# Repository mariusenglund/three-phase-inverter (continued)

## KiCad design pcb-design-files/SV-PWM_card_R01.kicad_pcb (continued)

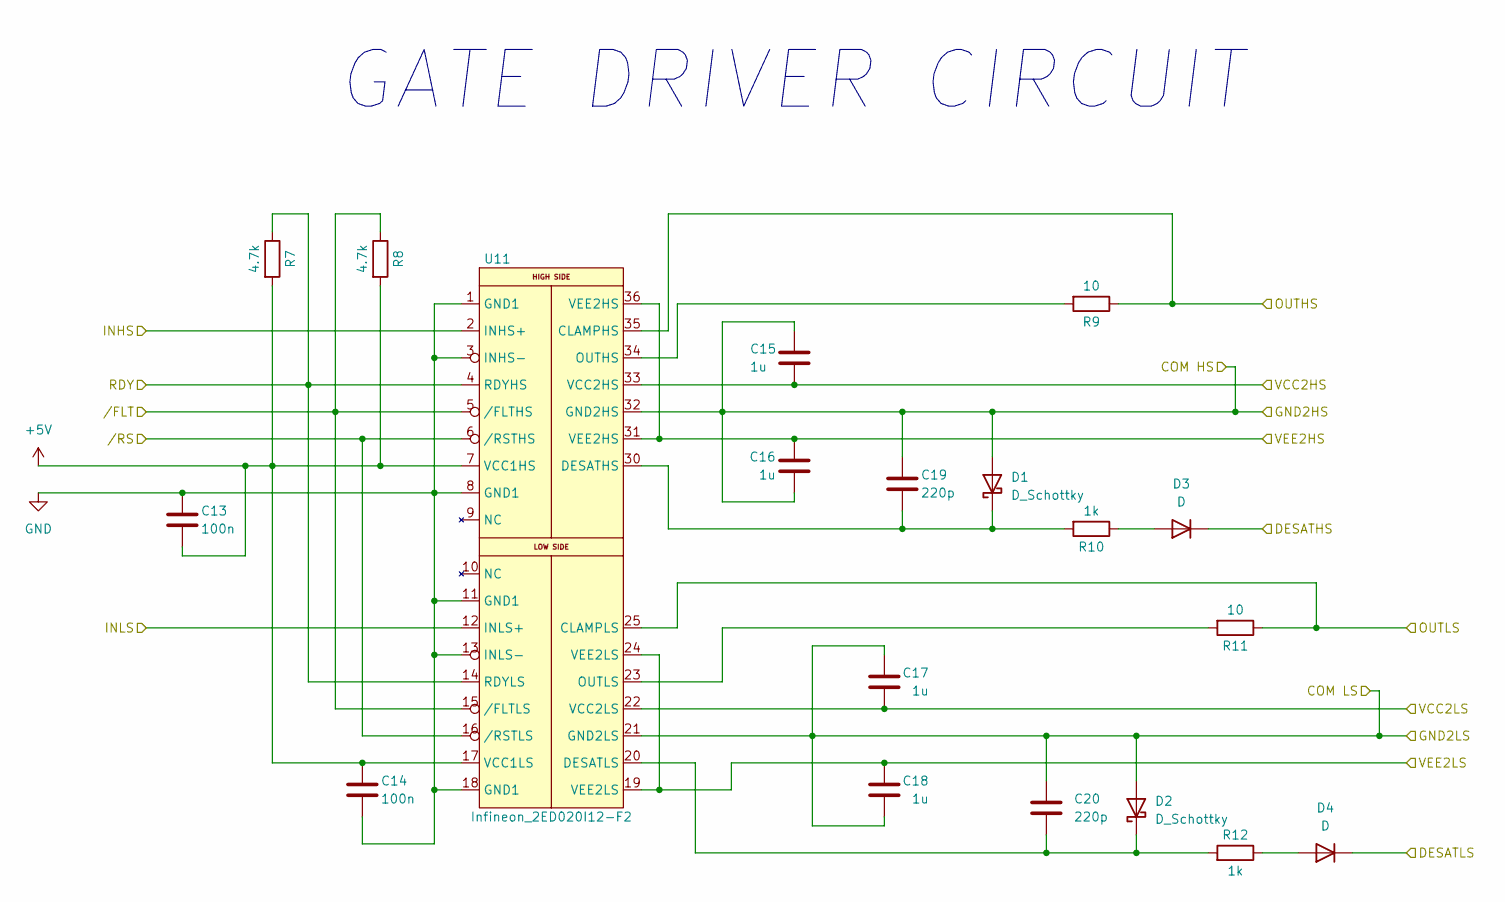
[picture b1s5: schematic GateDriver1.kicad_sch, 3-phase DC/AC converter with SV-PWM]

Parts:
C13, C14: 100n; C_1206_3216Metric_Pad1.33x1.80mm_HandSolder
C15, C16, C17, C18: 1u; C_1206_3216Metric_Pad1.33x1.80mm_HandSolder
C19, C20: 220p; C_1206_3216Metric_Pad1.33x1.80mm_HandSolder
D1, D2: D_Schottky; Schottky-BAT165AX
D3, D4: D; Diode-SMBJ50CA
R7, R8: 4.7k; R_1206_3216Metric_Pad1.30x1.75mm_HandSolder
R9, R11: 10; R_1206_3216Metric_Pad1.30x1.75mm_HandSolder
R10, R12: 1k; R_1206_3216Metric_Pad1.30x1.75mm_HandSolder
U11: Infineon_2ED020I12-F2; GateDriver-2ED020I12F2XUMA1

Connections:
+5V: C13.1, C14.2, R7.2, R8.2, U11.7 (VCC1HS), U11.17 (VCC1LS); also elsewhere on the board
+15 V (1): C17.1, U11.22 (VCC2LS); also elsewhere on the board
+15 V (2): C15.2, U11.33 (VCC2HS); also elsewhere on the board
-8.7 V (1): C18.1, U11.19 (VEE2LS), U11.24 (VEE2LS); also elsewhere on the board
-8.7 V (2): C16.1, U11.31 (VEE2HS), U11.36 (VEE2HS); also elsewhere on the board
/GateDriver1/OUTHS: R9.1, U11.35 (CLAMPHS); also elsewhere on the board
/GateDriver1/OUTLS: R11.1, U11.25 (CLAMPLS); also elsewhere on the board
COM (2): C15.1, C16.2, C19.2, D1.2 (A), D4.1 (K), U11.32 (GND2HS); also elsewhere on the board
GND: C13.2, C14.1, U11.1 (GND1), U11.3 (INHS-), U11.8 (GND1), U11.11 (GND1), U11.13 (INLS-), U11.18 (GND1); also elsewhere on the board
GND (dc-link): C17.2, C18.2, C20.2, D2.2 (A), U11.21 (GND2LS); also elsewhere on the board
I/O_DI_FLT-1: R8.1, U11.5 (/FLTHS), U11.15 (/FLTLS); also elsewhere on the board
I/O_DI_RDY-1: R7.1, U11.4 (RDYHS), U11.14 (RDYLS); also elsewhere on the board
I/O_DO_INHS-1: U11.2 (INHS+); also elsewhere on the board
I/O_DO_INLS-1: U11.12 (INLS+); also elsewhere on the board
I/O_DO_RS-1: U11.6 (/RSTHS), U11.16 (/RSTLS); also elsewhere on the board
unnamed: C19.1, D1.1 (K), R10.2, U11.30 (DESATHS)
unnamed: C20.1, D2.1 (K), R12.2, U11.20 (DESATLS)
unnamed: D3.2 (A), R10.1
unnamed: D4.2 (A), R12.1
unnamed: R9.2, U11.34 (OUTHS)
unnamed: R11.2, U11.23 (OUTLS)
TA+1_HS: D3.1 (K); also elsewhere on the board

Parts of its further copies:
C21, C22, C29, C30: 100n; C_1206_3216Metric_Pad1.33x1.80mm_HandSolder
C23, C24, C25, C26, C31, C32, C33, C34: 1u; C_1206_3216Metric_Pad1.33x1.80mm_HandSolder
C27, C28, C35, C36: 220p; C_1206_3216Metric_Pad1.33x1.80mm_HandSolder
D5, D6, D9, D10: D_Schottky; Schottky-BAT165AX
D7, D8, D11, D12: D; Diode-SMBJ50CA
R13, R14, R19, R20: 4.7k; R_1206_3216Metric_Pad1.30x1.75mm_HandSolder
R15, R17, R21, R23: 10; R_1206_3216Metric_Pad1.30x1.75mm_HandSolder
R16, R18, R22, R24: 1k; R_1206_3216Metric_Pad1.30x1.75mm_HandSolder
U12, U13: Infineon_2ED020I12-F2; GateDriver-2ED020I12F2XUMA1

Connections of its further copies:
+5V: C21.1, C22.2, C29.1, C30.2, R13.2, R14.2, R19.2, R20.2, U12.7 (VCC1HS), U12.17 (VCC1LS), U13.7 (VCC1HS), U13.17 (VCC1LS); also elsewhere on the board
+15 V (3): C25.1, U12.22 (VCC2LS); also elsewhere on the board
+15 V (4): C23.2, U12.33 (VCC2HS); also elsewhere on the board
+15 V (5): C33.1, U13.22 (VCC2LS); also elsewhere on the board
+15 V (6): C31.2, U13.33 (VCC2HS); also elsewhere on the board
-8.7 V (3): C26.1, U12.19 (VEE2LS), U12.24 (VEE2LS); also elsewhere on the board
-8.7 V (4): C24.1, U12.31 (VEE2HS), U12.36 (VEE2HS); also elsewhere on the board
-8.7 V (5): C34.1, U13.19 (VEE2LS), U13.24 (VEE2LS); also elsewhere on the board
-8.7 V (6): C32.1, U13.31 (VEE2HS), U13.36 (VEE2HS); also elsewhere on the board
/GateDriver2/OUTHS: R15.1, U12.35 (CLAMPHS); also elsewhere on the board
/GateDriver2/OUTLS: R17.1, U12.25 (CLAMPLS); also elsewhere on the board
/GateDriver3/OUTHS: R21.1, U13.35 (CLAMPHS); also elsewhere on the board
/GateDriver3/OUTLS: R23.1, U13.25 (CLAMPLS); also elsewhere on the board
COM (4): C23.1, C24.2, C27.2, D5.2 (A), D8.1 (K), U12.32 (GND2HS); also elsewhere on the board
COM (6): C31.1, C32.2, C35.2, D9.2 (A), D12.1 (K), U13.32 (GND2HS); also elsewhere on the board
GND: C21.2, C22.1, C29.2, C30.1, U12.1 (GND1), U12.3 (INHS-), U12.8 (GND1), U12.11 (GND1), U12.13 (INLS-), U12.18 (GND1), U13.1 (GND1), U13.3 (INHS-), U13.8 (GND1), U13.11 (GND1), U13.13 (INLS-), U13.18 (GND1); also elsewhere on the board
GND (dc-link): C25.2, C26.2, C28.2, C33.2, C34.2, C36.2, D6.2 (A), D10.2 (A), U12.21 (GND2LS), U13.21 (GND2LS); also elsewhere on the board
I/O_DI_FLT-2: R14.1, U12.5 (/FLTHS), U12.15 (/FLTLS); also elsewhere on the board
I/O_DI_FLT-3: R20.1, U13.5 (/FLTHS), U13.15 (/FLTLS); also elsewhere on the board
I/O_DI_RDY-2: R13.1, U12.4 (RDYHS), U12.14 (RDYLS); also elsewhere on the board
I/O_DI_RDY-3: R19.1, U13.4 (RDYHS), U13.14 (RDYLS); also elsewhere on the board
I/O_DO_INHS-2: U12.2 (INHS+); also elsewhere on the board
I/O_DO_INHS-3: U13.2 (INHS+); also elsewhere on the board
I/O_DO_INLS-2: U12.12 (INLS+); also elsewhere on the board
I/O_DO_INLS-3: U13.12 (INLS+); also elsewhere on the board
I/O_DO_RS-2: U12.6 (/RSTHS), U12.16 (/RSTLS); also elsewhere on the board
I/O_DO_RS-3: U13.6 (/RSTHS), U13.16 (/RSTLS); also elsewhere on the board
unnamed: C27.1, D5.1 (K), R16.2, U12.30 (DESATHS)
unnamed: C28.1, D6.1 (K), R18.2, U12.20 (DESATLS)
unnamed: C35.1, D9.1 (K), R22.2, U13.30 (DESATHS)
unnamed: C36.1, D10.1 (K), R24.2, U13.20 (DESATLS)
unnamed: D7.2 (A), R16.1
unnamed: D8.2 (A), R18.1
unnamed: D11.2 (A), R22.1
unnamed: D12.2 (A), R24.1
unnamed: R15.2, U12.34 (OUTHS)
unnamed: R17.2, U12.23 (OUTLS)
unnamed: R21.2, U13.34 (OUTHS)
unnamed: R23.2, U13.23 (OUTLS)
TA+1_HS: D7.1 (K), D11.1 (K); also elsewhere on the board

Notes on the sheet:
GATE DRIVER CIRCUIT

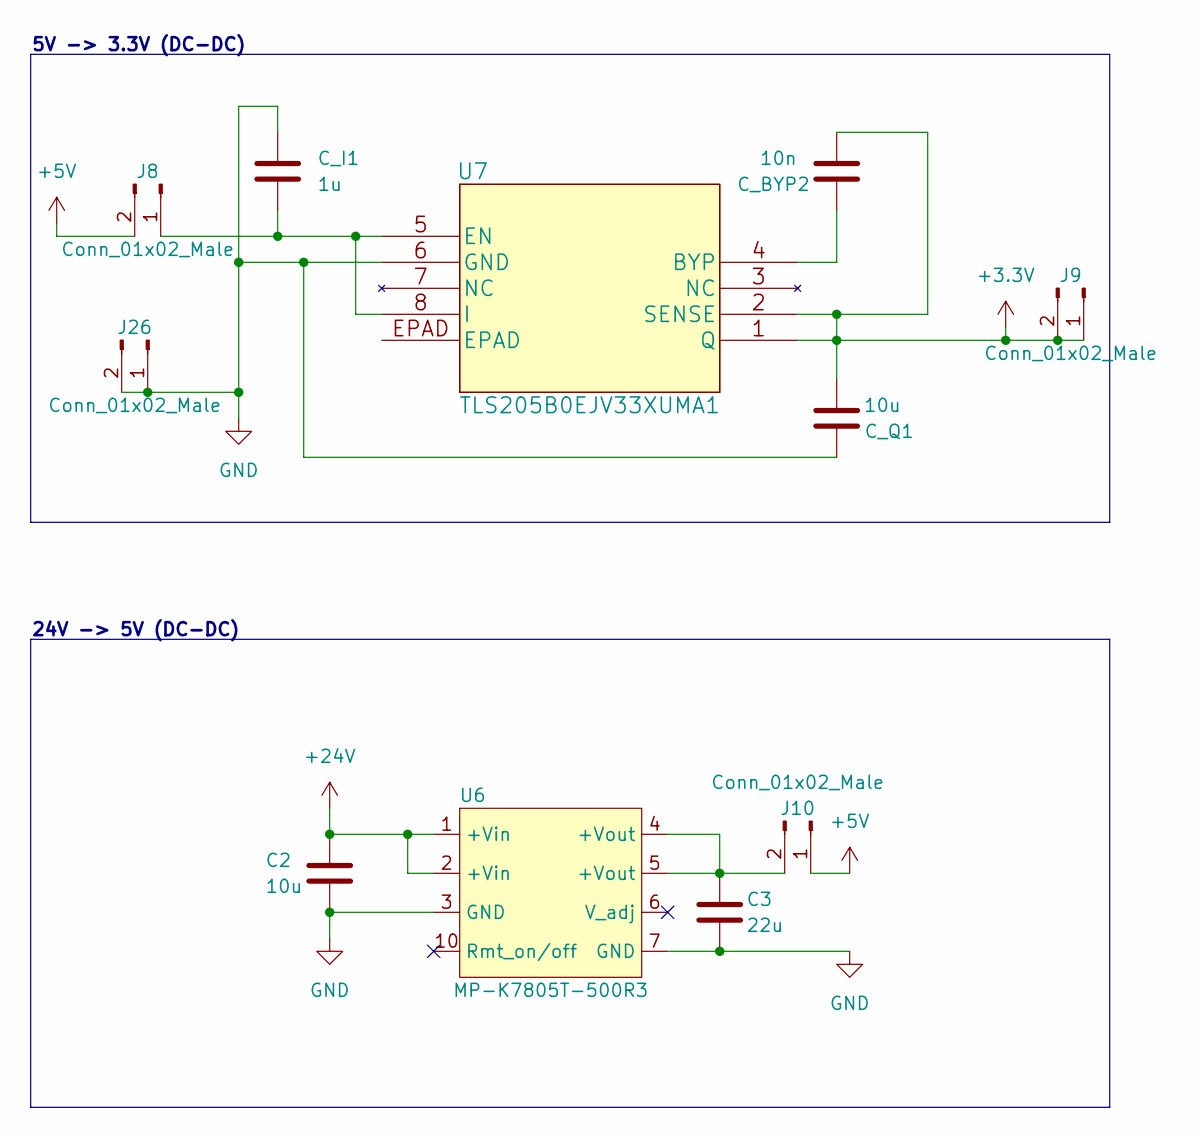
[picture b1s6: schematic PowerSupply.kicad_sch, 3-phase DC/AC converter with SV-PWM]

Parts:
C2: 10u; C_1206_3216Metric_Pad1.33x1.80mm_HandSolder
C3: 22u; C_1206_3216Metric_Pad1.33x1.80mm_HandSolder
C_BYP2: 10n; C_1206_3216Metric_Pad1.33x1.80mm_HandSolder
C_I1: 1u; C_1206_3216Metric_Pad1.33x1.80mm_HandSolder
C_Q1: 10u; C_1206_3216Metric_Pad1.33x1.80mm_HandSolder
J8, J9, J10, J26: Conn_01x02_Male; PinHeader_1x02_P1.00mm_Vertical
U6: MP-K7805T-500R3; Multicomp-MPK7803T500R3
U7: TLS205B0EJV33XUMA1; TLS205B0EJV33XUMA1-SOIC127P600X170-9N

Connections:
+3.3V: C_BYP2.2, C_Q1.2, J9.1, J9.2, U7.1 (Q), U7.2 (SENSE); also elsewhere on the board
+5V: J8.2, J10.1; also elsewhere on the board
+24V: C2.1, U6.1 (+Vin), U6.2 (+Vin); also elsewhere on the board
GND: C2.2, C3.2, C_I1.2, C_Q1.1, J26.1, J26.2, U6.3 (GND), U6.7 (GND), U7.6 (GND); also elsewhere on the board
unnamed: C3.1, J10.2, U6.4 (+Vout), U6.5 (+Vout)
unnamed: C_BYP2.1, U7.4 (BYP)
unnamed: C_I1.1, J8.1, U7.5 (EN), U7.8 (I)

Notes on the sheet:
24V -> 5V (DC-DC)
5V -> 3.3V (DC-DC)

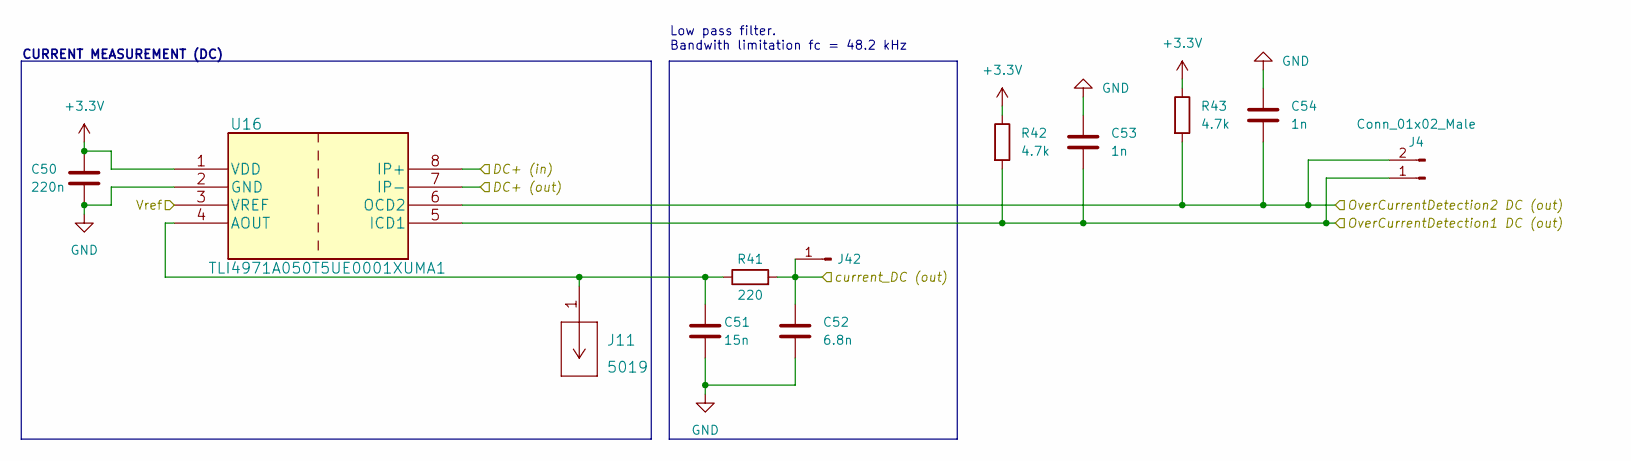
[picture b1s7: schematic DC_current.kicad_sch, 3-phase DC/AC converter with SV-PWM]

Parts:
C50: 220n; C_1206_3216Metric_Pad1.33x1.80mm_HandSolder
C51: 15n; C_1206_3216Metric_Pad1.33x1.80mm_HandSolder
C52: 6.8n; C_1206_3216Metric_Pad1.33x1.80mm_HandSolder
C53, C54: 1n; C_1206_3216Metric_Pad1.33x1.80mm_HandSolder
J4: Conn_01x02_Male; PinHeader_1x02_P1.00mm_Vertical
J11: 5019; Keystone-5019
J42: Conn_01x01_Male; PinHeader_1x01_P1.00mm_Vertical
R41: 220; R_1206_3216Metric_Pad1.30x1.75mm_HandSolder
R42, R43: 4.7k; R_1206_3216Metric_Pad1.30x1.75mm_HandSolder
U16: TLI4971A050T5UE0001XUMA1

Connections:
+3.3V: C50.2, R42.1, R43.1, U16.1 (VDD), U16.9; also elsewhere on the board
/Braking/DC-LINK (+): U16.8 (IP+); also elsewhere on the board
GND: C50.1, C51.2, C52.2, C53.1, C54.1, U16.2 (GND); also elsewhere on the board
I/O_AI_current-dc: C52.1, J42.1, R41.2; also elsewhere on the board
I/O_AI_vcc-io: U16.3 (VREF); also elsewhere on the board
I/O_DI_ocd1-dc: C53.2, J4.1, R42.2, U16.5 (ICD1); also elsewhere on the board
I/O_DI_ocd2-dc: C54.2, J4.2, R43.2, U16.6 (OCD2); also elsewhere on the board
unnamed: C51.1, J11.1, R41.1, U16.4 (AOUT)
TA+1_HS: U16.7 (IP-); also elsewhere on the board

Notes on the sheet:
Low pass filter. Bandwith limitation fc = 48.2 kHz
CURRENT MEASUREMENT (DC)

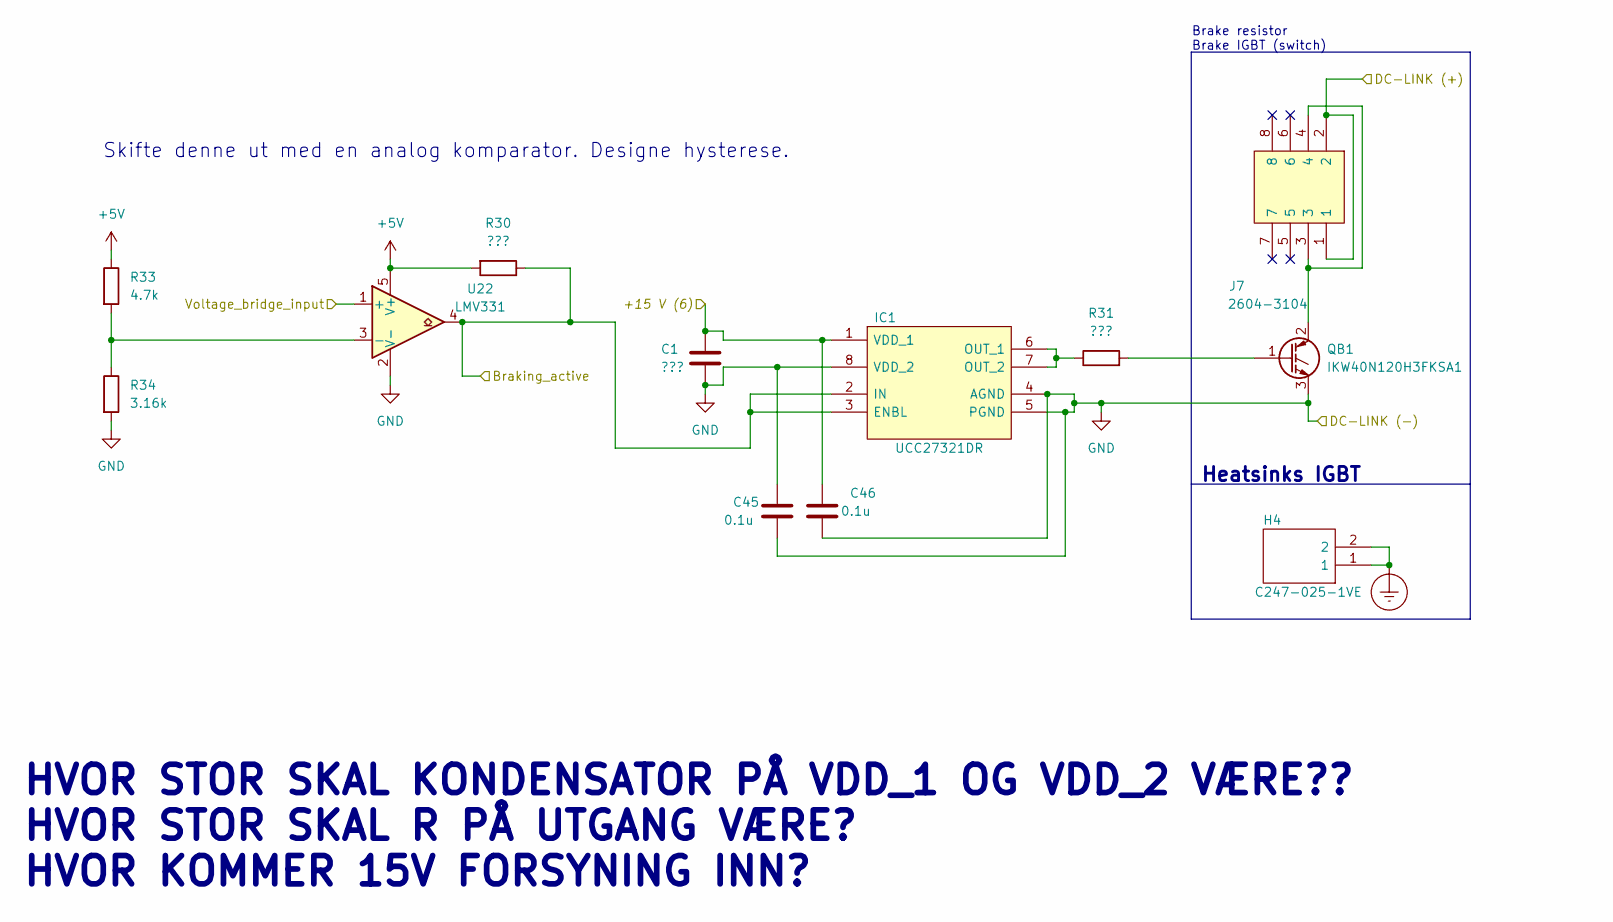
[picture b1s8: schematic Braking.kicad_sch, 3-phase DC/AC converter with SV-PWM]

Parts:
C1: ???; C_1206_3216Metric_Pad1.33x1.80mm_HandSolder
C45, C46: 0.1u; C_1206_3216Metric_Pad1.33x1.80mm_HandSolder
H4: C247-025-1VE; Heatsink_brake_C2470251VE; Manufacturer_Part_Number C247-025-1VE; Mouser Part Number 588-C247-025-1VE
IC1: UCC27321DR; UCC27321DR_SOIC127P600X175-8N; Manufacturer_Part_Number UCC27321DR; Mouser Part Number 595-UCC27321DR
J7: 2604-3104; WAGO-26043104; Manufacturer_Part_Number 2604-3104
QB1: IKW40N120H3FKSA1; IGBT-TO544P521X1592X2557-3P
R30, R31: ???; R_1206_3216Metric_Pad1.30x1.75mm_HandSolder
R33: 4.7k; R_1206_3216Metric_Pad1.30x1.75mm_HandSolder
R34: 3.16k; R_1206_3216Metric_Pad1.30x1.75mm_HandSolder
U22: LMV331; LMV331M5_SOT95P280X145-5N

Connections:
+5V: R30.2, R33.1, U22.5 (V+); also elsewhere on the board
+15 V (6): C1.1, C46.1, IC1.1 (VDD_1); also elsewhere on the board
/Braking/DC-LINK (+): J7.1, J7.2; also elsewhere on the board
DC-LINK-VOLTAGE: U22.1 (+); also elsewhere on the board
Earth_Protective: H4.1, H4.2; also elsewhere on the board
GND (dc-link): C1.2, C45.1, C45.2, C46.2, IC1.4 (AGND), IC1.5 (PGND), IC1.8 (VDD_2), QB1.3 (E), R34.2, U22.2 (V-); also elsewhere on the board
I/O_DI_braking-active: IC1.2 (IN), IC1.3 (ENBL), R30.1, U22.4; also elsewhere on the board
unnamed: IC1.6 (OUT_1), IC1.7 (OUT_2), R31.1
unnamed: J7.3, J7.4, QB1.2 (C)
unnamed: QB1.1 (G), R31.2
unnamed: R33.2, R34.1, U22.3 (-)

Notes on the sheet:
Skifte denne ut med en analog komparator. Designe hysterese.
HVOR STOR SKAL KONDENSATOR PÅ VDD_1 OG VDD_2 VÆRE?? HVOR STOR SKAL R PÅ UTGANG VÆRE? HVOR KOMMER 15V FORSYNING INN?
Brake resistor Brake IGBT (switch)
Heatsinks IGBT

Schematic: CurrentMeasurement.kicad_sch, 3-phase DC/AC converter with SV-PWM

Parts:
C4, C5, C6: 220n; C_1206_3216Metric_Pad1.33x1.80mm_HandSolder
C7, C8, C9, C10, C11, C12: 1n; C_1206_3216Metric_Pad1.33x1.80mm_HandSolder
C37, C38, C42, C43, C44: 6.8n; C_1206_3216Metric_Pad1.33x1.80mm_HandSolder
C39, C40, C41: 15n; C_1206_3216Metric_Pad1.33x1.80mm_HandSolder
J1, J2, J3, J27: Conn_01x02_Male; PinHeader_1x02_P1.00mm_Vertical
J13, J14, J15: 5019; Keystone-5019
J23, J24, J34, J43: Conn_01x01_Male; PinHeader_1x01_P1.00mm_Vertical
R1, R2, R3, R4, R46, R47: 4.7k; R_1206_3216Metric_Pad1.30x1.75mm_HandSolder
R25, R26: 1k; R_1206_3216Metric_Pad1.30x1.75mm_HandSolder
R27, R28, R29: 220; R_1206_3216Metric_Pad1.30x1.75mm_HandSolder
U8, U9, U10: TLI4971A050T5UE0001XUMA1

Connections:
+3.3V: C4.1, C5.1, C6.1, J27.1, R1.1, R2.1, R3.1, R4.1, R25.1, R46.1, R47.1, U8.1 (VDD), U8.9, U9.1 (VDD), U9.9, U10.1 (VDD), U10.9; also elsewhere on the board
/CurrentMeasurement/L1 (out): U10.7 (IP-); also elsewhere on the board
/CurrentMeasurement/L2 (out): U9.7 (IP-); also elsewhere on the board
/CurrentMeasurement/L3 (out): U8.7 (IP-); also elsewhere on the board
COM (2): U10.8 (IP+); also elsewhere on the board
COM (4): U9.8 (IP+); also elsewhere on the board
COM (6): U8.8 (IP+); also elsewhere on the board
GND: C4.2, C5.2, C6.2, C7.1, C8.1, C9.1, C10.1, C11.1, C12.1, C37.2, C38.2, C39.2, C40.2, C41.2, C42.2, C43.2, C44.2, J27.2, R26.2, U8.2 (GND), U9.2 (GND), U10.2 (GND); also elsewhere on the board
I/O_AI_current-L1: C42.1, J23.1, R27.2; also elsewhere on the board
I/O_AI_current-L2: C43.1, J24.1, R28.2; also elsewhere on the board
I/O_AI_current-L3: C44.1, J34.1, R29.2; also elsewhere on the board
I/O_AI_vcc-io: C37.1, C38.1, J43.1, R25.2, R26.1, U8.3 (VREF), U9.3 (VREF), U10.3 (VREF); also elsewhere on the board
I/O_DI_ocd1-L1: C7.2, J1.1, R1.2, U10.5 (ICD1); also elsewhere on the board
I/O_DI_ocd1-L2: C8.2, J2.1, R2.2, U9.5 (ICD1); also elsewhere on the board
I/O_DI_ocd1-L3: C9.2, J3.1, R3.2, U8.5 (ICD1); also elsewhere on the board
I/O_DI_ocd2-L1: C10.2, J1.2, R4.2, U10.6 (OCD2); also elsewhere on the board
I/O_DI_ocd2-L2: C11.2, J2.2, R46.2, U9.6 (OCD2); also elsewhere on the board
I/O_DI_ocd2-L3: C12.2, J3.2, R47.2, U8.6 (OCD2); also elsewhere on the board
unnamed: C39.1, J13.1, R27.1, U10.4 (AOUT)
unnamed: C40.1, J14.1, R28.1, U9.4 (AOUT)
unnamed: C41.1, J15.1, R29.1, U8.4 (AOUT)

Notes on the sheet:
Power supply from jumpers
Low pass filter. Bandwith limitation fc = 48.2 kHz
CURRENT MEASUREMENTS: L1-L2-L3
REFERENCE VOLTAGE - CURRENT CHIPS / ADC

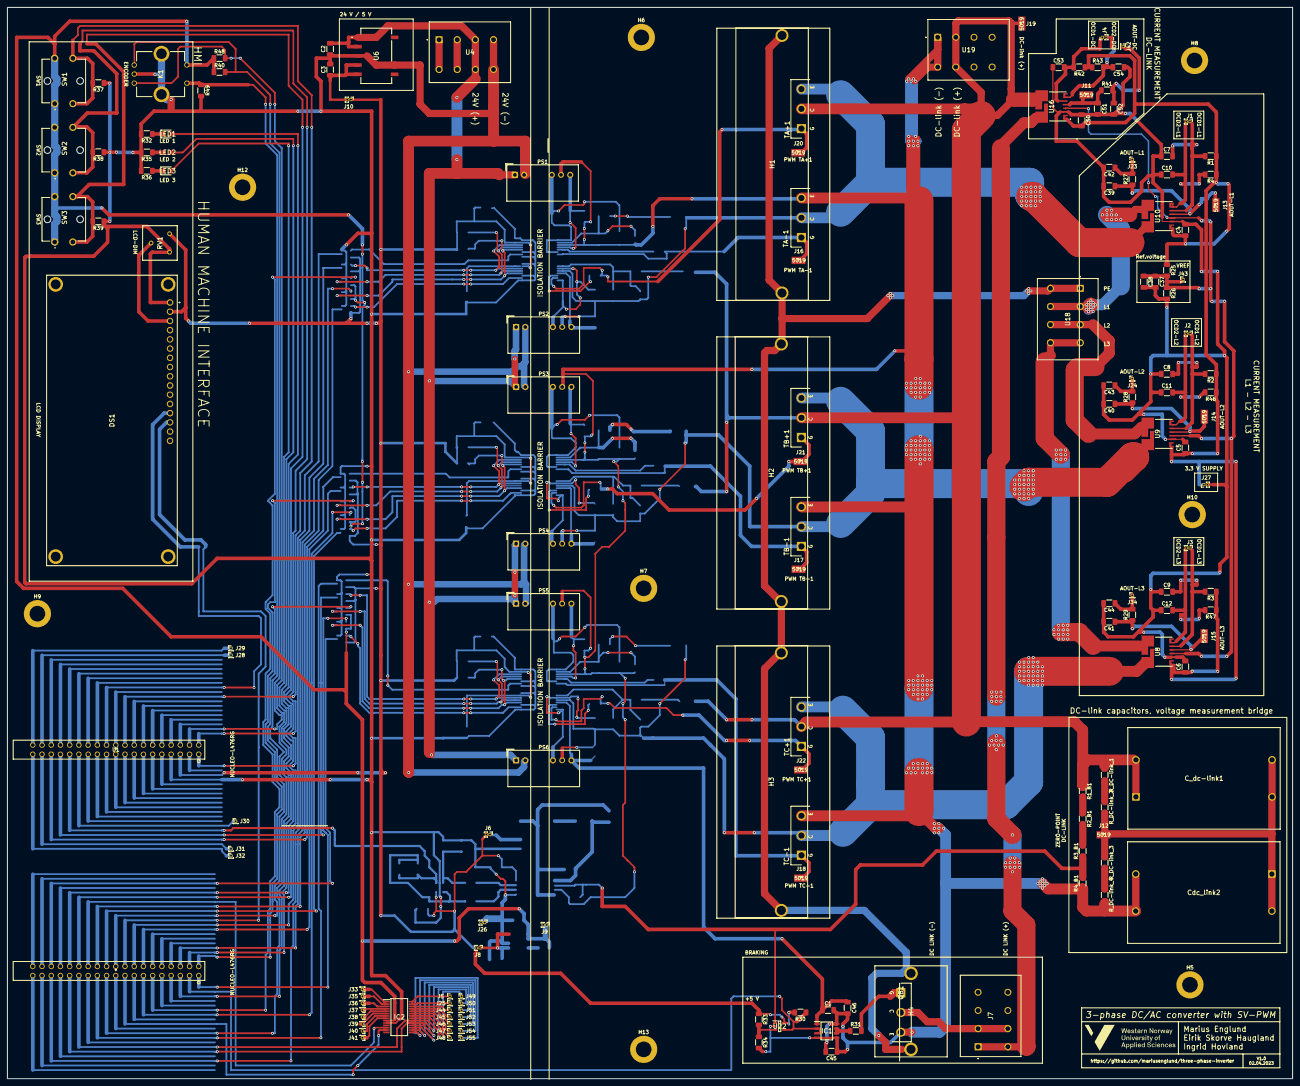
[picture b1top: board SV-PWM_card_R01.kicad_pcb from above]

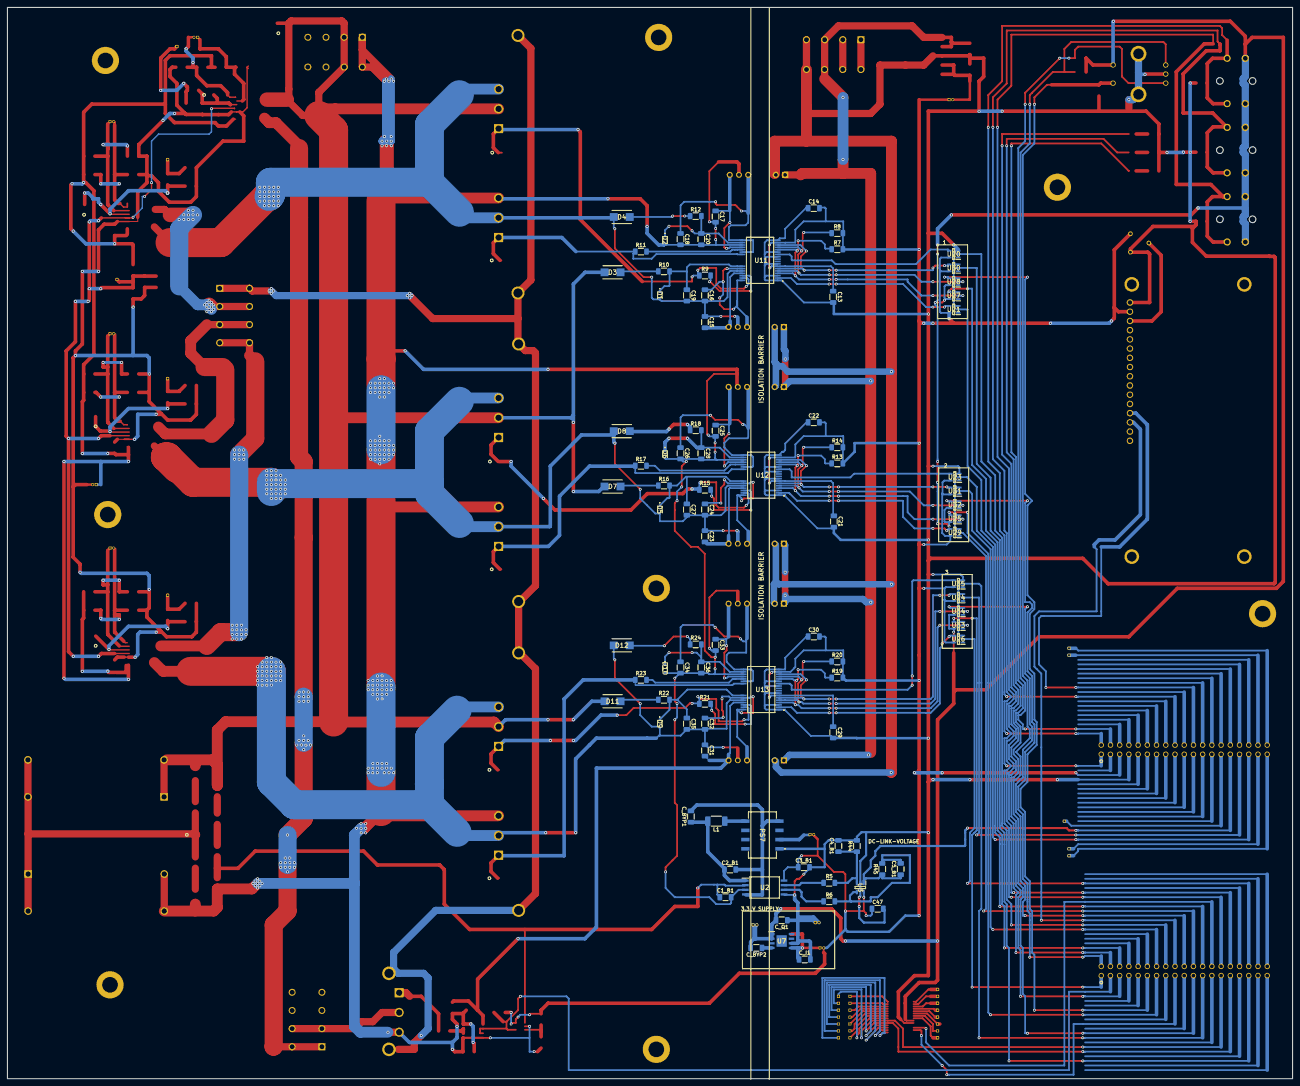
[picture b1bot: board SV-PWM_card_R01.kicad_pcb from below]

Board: 2 copper layers, 354.0 x 295.1 mm, 256 parts (91 on the bottom side), 153 nets.

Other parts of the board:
H5: MountingHole; MountingHole_4.3mm_M4_DIN965_Pad
